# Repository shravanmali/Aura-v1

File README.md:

# Aura v1: Autonomous Companion Rover & Bedroom Satellite Pod

> *A comprehensive overview of the Aura v1 system architecture, bench-tested hardware, and software implementation in a single document.*

Hi! I'm Shravan Mali, an 18-year-old student and maker from India. This is **Aura v1**, an autonomous companion robot and bedroom satellite pod I am building from scratch for [Hack Club Fallen](https://fallen.hackclub.com/projects/prj_kV1Fde).

The idea behind Aura is to build a helpful robot for my room. It has two main parts:
1. **The Rover:** A 4WD mobile robot that tracks and follows me around the room using a camera, checks temperature and humidity, acts as a night motion sentry, and can count workout reps or play music on command.
2. **The Bedroom Satellite Pod:** A small stationary device plugged into the wall in my room. It connects to the rover over local Wi-Fi, listens for voice commands, controls my room's AC with an infrared transmitter, and lets me summon the rover to my room just by saying *"Aura, come here"*.

---

## Videos that shows physically working project.

I test and verify everything on my physical desk before moving to the next step. Here are three videos of the project working right on my desk:

1. **Live Vision Tracking & HUD:** [Watch on YouTube Shorts](https://youtube.com/shorts/xNkBhOSDpR0)  
   *(The rover tracks me by turning its BO motors left and right while streaming real-time temperature, humidity, and PIR motion data to my laptop screen).*
2. **DHT11 & PIR Motion Sensor Test:** [Watch on YouTube Shorts](https://youtube.com/shorts/FN-GSGQxdE8)  
   *(Bench testing room climate readings and motion detection on the ESP32-S3 before connecting the motor driver).*
3. **Face Centroid Tracking Loop:** [Watch on YouTube](https://youtu.be/JqQfvNIkbz4)  
   *(Testing real-time pixel offset calculations to steer the motors smoothly over serial).*

---

## What I've Built & Verified on My Desk

- **4WD Skid-Steer Motors:** 4x 200 RPM BO geared motors running on an L298N motor driver with ESP32 PWM soft-start so the motors don't jerk.
- **Real-Time Vision Following:** An OpenCV Python script (`vision_tracker.py`) that tracks human movement from a phone/webcam stream and steers the motors over USB serial at 115,200 baud.
- **Room Telemetry & Sentry:** A DHT11 sensor logging temperature and humidity every 2 seconds, plus a PIR motion sensor that triggers an alert badge if someone walks into the room.
- **Bedroom Satellite Pod PCB (v1.0):** A custom 2-layer PCB designed in KiCad. It houses the ESP32-C3 SuperMini, INMP441 mic, MAX98357A 3W amplifier, a 470µF bulk capacitor (to stop the speaker from rebooting the ESP32), an IR blaster, and an RGB LED ring. It passed KiCad DRC with **0 errors and 0 unconnected items**, and the fabrication Gerbers are ready.
- **Rover Carrier Board v1.5 Schematic:** The rover's motherboard schematic, verified with **0 ERC errors**. It separates high-current servo power from sensitive logic, adds I2S audio headers, and includes a 100kΩ/33kΩ resistor divider to monitor the 11.1V battery.
- **3D Chassis:** A dual-deck chassis designed in OpenSCAD to hold the motors, battery pack, electronics, and camera pan-tilt bracket.

---

## Features Coming Next (In Progress)

- **Exercise Rep Counter:** Using MediaPipe pose tracking on the camera to count push-ups or squats and check workout form.
- **Voice Music Playback:** Playing songs and voice responses through the I2S amplifier and 3W speaker via voice commands.
- **Auto-Docking:** Using the camera to detect an ArUco marker on a charging dock so the rover can drive itself to charge when the battery drops below 15% (`ADC <= 2940`).
- **Smart AC Control:** Blasting 940nm IR remote codes to turn the room AC on or off based on live temperature readings from the DHT11 sensor.

---

## How the System Works

```text
┌─────────────────────────────────────────────────────────────┐
│             AURA V1 AUTONOMOUS MOBILE ROVER                 │
│                                                             │
│   [ Raspberry Pi 4 Model B (1GB RAM) ]                      │
│   • High-Level Brain, OpenCV Computer Vision, Voice AI      │
│   • MediaPipe Pose Tracking (Exercise Rep Counter)          │
│   • ArUco Marker Autonomous Docking Navigation              │
│                              ▲                              │
│                              │ High-Speed UART / Serial     │
│                              ▼                              │
│   [ ESP32-S3 DevKit-C (N16R8) ]                             │
│   • Instant Real-Time Motor Kinematics (4WD PWM)            │
│   • 2-Axis Pan-Tilt Gimbal Servos (MG90S)                   │
│   • HC-SR04 Ultrasonic Emergency Braking (<1ms stop)        │
│   • 11.1V Battery Fuel Gauge ADC Monitor (Auto-dock <= 15%) │
└──────────────────────────────┬──────────────────────────────┘
                               ▲
                               │ Local Wi-Fi Mesh
                               ▼
┌─────────────────────────────────────────────────────────────┐
│             AURA BEDROOM SATELLITE POD                      │
│                                                             │
│   [ Stationary ESP32-C3 SuperMini Node (5V USB-C Powered) ] │
│   • 24/7 Room Listening Station (INMP441 + MAX98357A)       │
│   • Voice-Command Music & Media Playback (3W Speaker)       │
│   • Dedicated Room ID ("Aura, come here" summoning)         │
│   • 940nm IR Blaster + DHT11 Closed-Loop Room AC Control    │
│   • 470µF Bulk Capacitor (Prevents speaker inrush brownouts)│
└─────────────────────────────────────────────────────────────┘
```

---

## Custom KiCad Hardware & PCBs

All PCB design files, schematics, and manufacturing Gerbers are open-source in the [`hardware/`](hardware/) directory:

### 1. Bedroom Satellite Pod v1.0 (Fabrication-Ready PCB)
* **Directory:** [`hardware/Aura_Satellite_Pod/`](hardware/Aura_Satellite_Pod/)
* **Features:** 2-layer board, dual copper ground planes, 15.24mm DIP socket spacing for ESP32-C3 SuperMini, anti-brownout audio filtering, and 4 corner M3 mounting holes.
* **Status:** **0 DRC Errors, 0 Unconnected Nets**.
* **Files:** [Schematic PDF](hardware/Aura_Satellite_Pod/Aura_Satellite_Pod_Schematic.pdf) | [Manufacturing Gerbers Zip](hardware/Aura_Satellite_Pod/Gerbers_Aura_Satellite_Pod_v1.0.zip) | [3D Front Render](hardware/Aura_Satellite_Pod/3d_pcb_front.png) | [3D Back Render](hardware/Aura_Satellite_Pod/3d_pcb_back.png)

### 2. Rover Carrier Motherboard (Final Production PCB)
* **Directory:** [`hardware/Aura_Rover_Carrier_Final/`](hardware/Aura_Rover_Carrier_Final/)
* **Features:**
  * **Dual Isolated Power Rails:** Dedicated 5.1V logic rail (Buck #1 XL4015) for Raspberry Pi 4B & audio, and 5.0V actuator rail (Buck #2 LM2596S) with a 470µF bulk capacitor for MG90S servos and NeoPixels.
  * **Reverse Polarity & Auto-Docking Protection:** `AO3401A` / `IRF9540N` P-channel MOSFET circuit (0.03V drop) and `SS54` Schottky diode protecting dock charging contacts.
  * **High-Current Motor Rail:** Heavy screw terminal (`J_MOTOR`) powering L298N drive motors directly from 11.1V battery.
  * **Raspberry Pi Hardware Watchdog:** NPN transistor circuit (`Q4` 2N2222) to hardware-reset Linux via `GLOBAL_EN` if a lockup occurs.
  * **Visual Diagnostics & Alerts:** 3 power LEDs (Green 11.1V, Blue 5V, Amber 5V Servo), 5V active piezo buzzer, and I2C sensor expansion port.
* **Status:** **0 ERC Errors, 100% Routed (0 Unconnected Items), 0 DRC Violations, JLCPCB Manufacturing Gerbers Ready**.
* **Files:** [KiCad Schematic](hardware/Aura_Rover_Carrier_Final/Aura_Rover_Carrier_Final.kicad_sch) | [Schematic PDF](hardware/Aura_Rover_Carrier_Final/Aura_Rover_Carrier_Final_Schematic.pdf) | [PCB File](hardware/Aura_Rover_Carrier_Final/Aura_Rover_Carrier_Final.kicad_pcb) | [Manufacturing Gerbers Zip](hardware/Aura_Rover_Carrier_Final/Gerbers_Aura_Rover_Carrier_Final.zip) | [BOM CSV](hardware/Aura_Rover_Carrier_Final/Aura_Rover_Carrier_Final_BOM.csv) | [3D Top View](hardware/Aura_Rover_Carrier_Final/3d_pcb_carrier_top.png) | [3D Isometric View](hardware/Aura_Rover_Carrier_Final/3d_pcb_carrier_iso.png)

### 3. Historical Iteration Archive
All prior hardware revisions from prototype v1.0 through v1.5 are preserved in [`hardware/archive/`](hardware/archive/).

---

## Bill of Materials 

I keep two separate BOM files to be 100% transparent about what I already have on my desk and what I need funding for from Hack Club:

1. **[BOM.md](BOM.md) (Hack Club Fallen Grant Request):**  
   The exact 17 audited items requested through the Hack Club Fallen virtual card totaling **₹9,528 (~$100.67 USD)**, with clickable vendor purchase links for reviewers.
2. **[Aura_Master_BOM.csv](Aura_Master_BOM.csv) (Complete 0-to-100 Hardware Inventory):**  
   The complete system build (32 subsystems totaling ₹11,848), clearly separating:
   * **Owned by me (I have on my desk):** ₹2,320 (15 subsystems: ESP32-S3, BO motors, wheels, L298N, chassis, sensors, passives).
   * **Requested from Hack Club Fallen:** ₹9,528 (17 subsystems: Pi 4, CSI camera, MG90S servos, Li-ion 18650 pack, BMS, charger, satellite components).

---

## 3D Chassis Design

The chassis is designed in OpenSCAD with dual-deck standoffs to hold the battery pack, motor drivers, and boards securely:

---

## How to Run Locally

### 1. Upload Microcontroller Firmware
Open this repository in VS Code with PlatformIO:
```powershell
pio run --target upload --upload-port COM6
```
*(Or open `src/main.cpp` in Arduino IDE, select ESP32-S3 Dev Module, and upload).*

### 2. Start the Computer Vision Dashboard
1. Open DroidCam on your phone (or plug in a USB webcam).
2. Run the tracking script on your computer:
```powershell
python vision_tracker.py
```
* **Keyboard Driving:** Press **W / A / S / D** to drive manually, **Spacebar** to brake, **Q** to quit.
* **Auto-Follow:** Stand in front of the camera; the BO motors will automatically steer left/right to keep you centered.

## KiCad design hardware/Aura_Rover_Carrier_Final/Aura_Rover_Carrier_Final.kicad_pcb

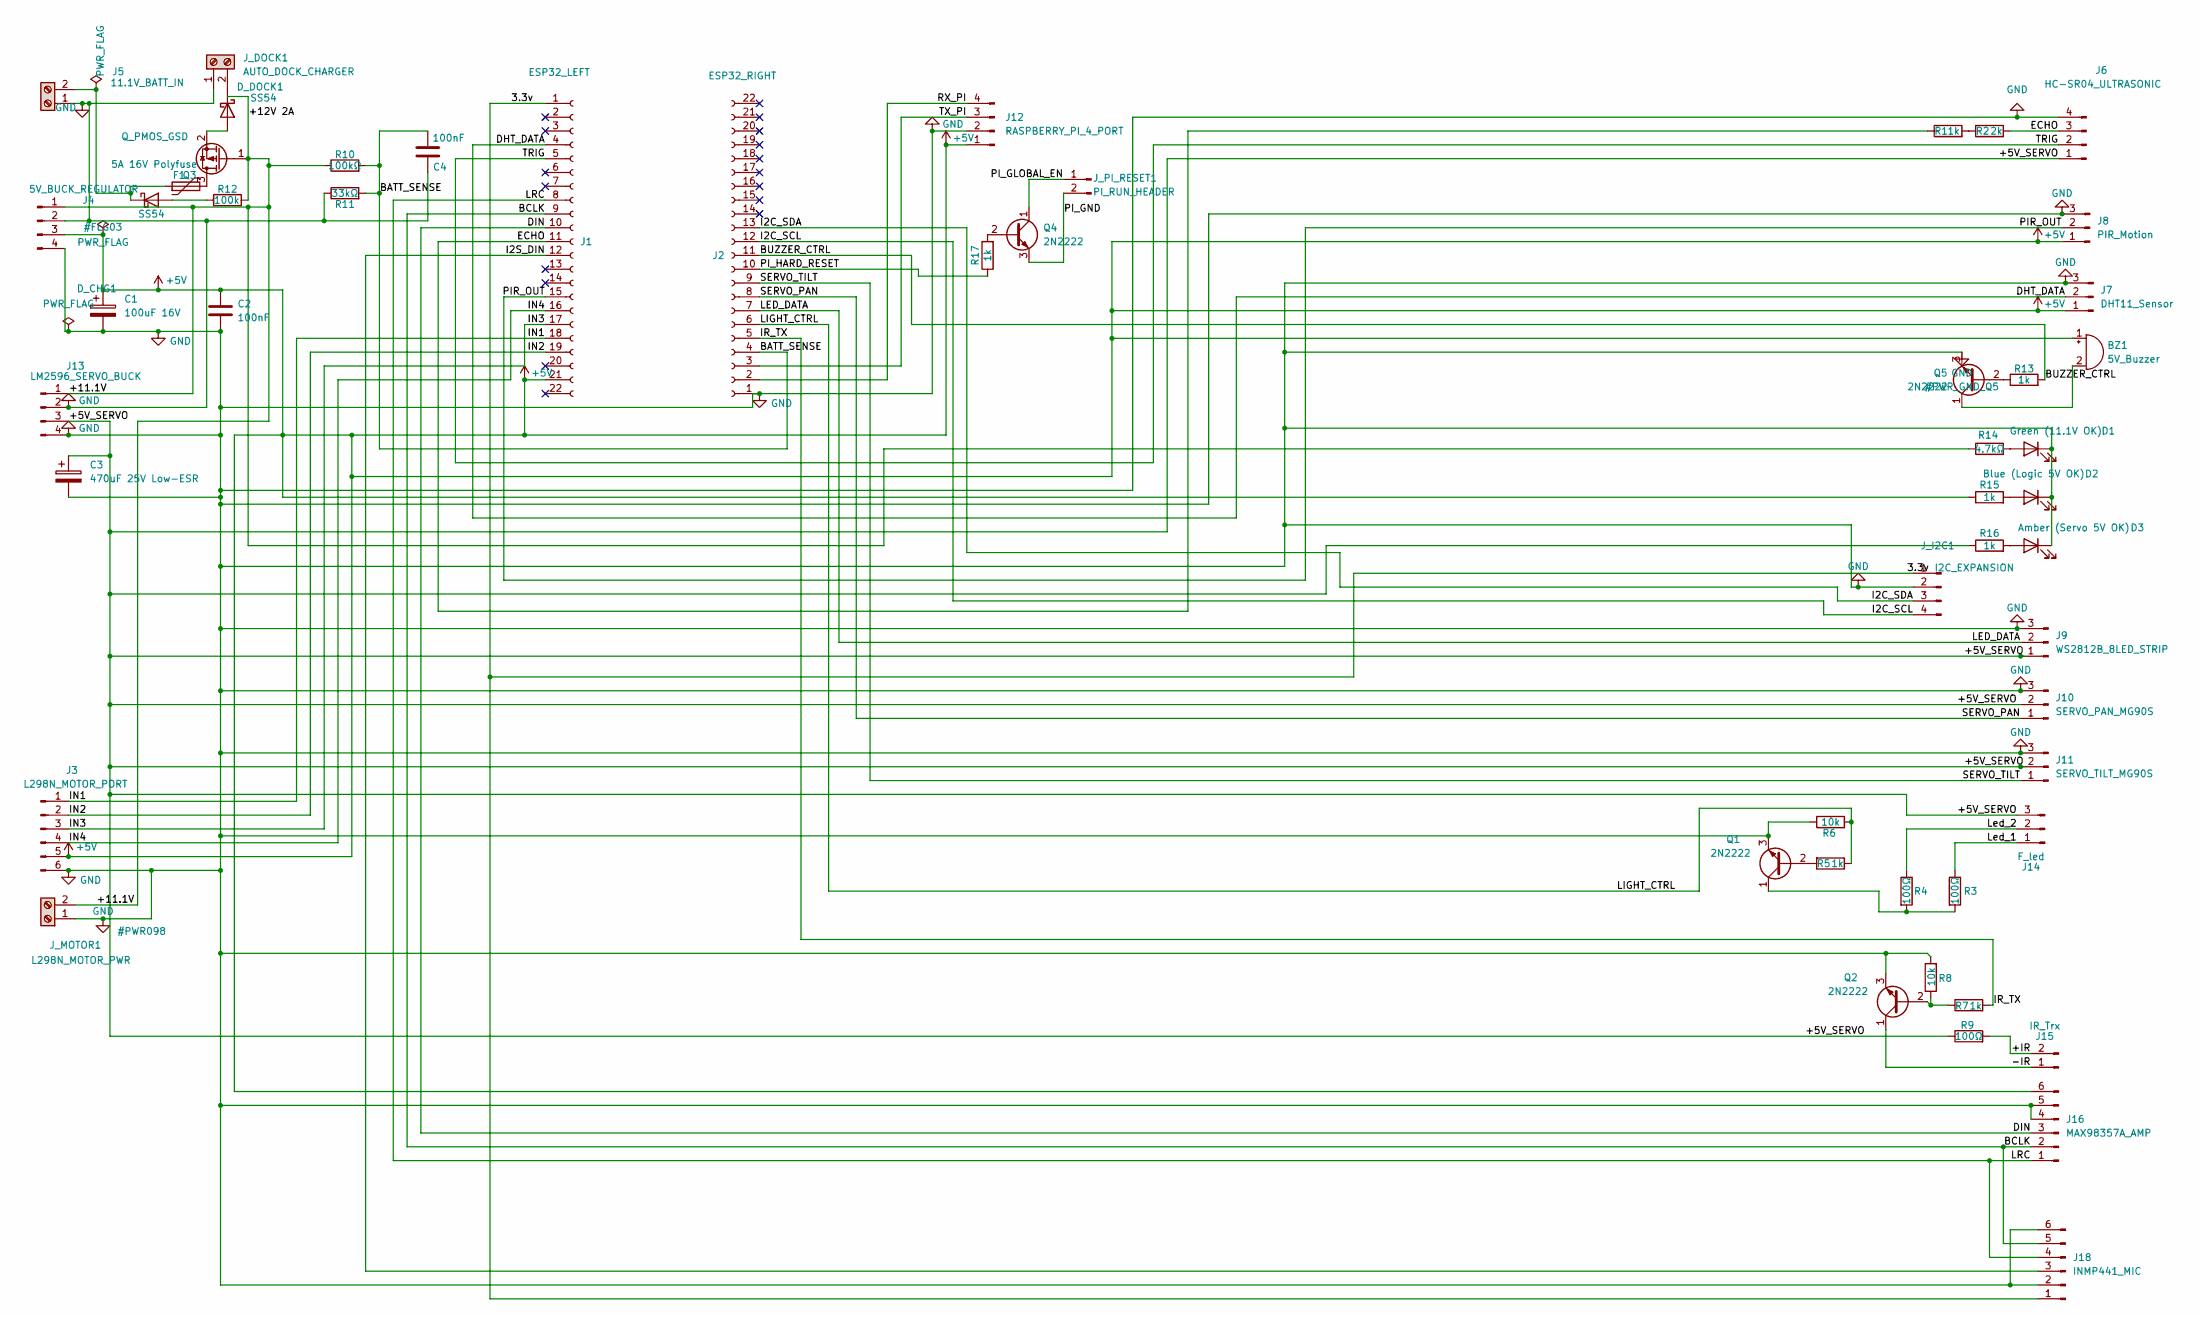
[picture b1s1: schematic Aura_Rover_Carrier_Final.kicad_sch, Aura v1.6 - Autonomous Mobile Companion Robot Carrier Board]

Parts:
BZ1: 5V_Buzzer; Buzzer_12x9.5RM7.6
C1: 100uF 16V; CP_Radial_D6.3mm_P2.50mm
C2, C4: 100nF; C_Disc_D5.0mm_W2.5mm_P5.00mm
C3: 470uF 25V Low-ESR; CP_Radial_D8.0mm_P3.50mm
D1: Green (11.1V OK); LED_D3.0mm
D2: Blue (Logic 5V OK); LED_D3.0mm
D3: Amber (Servo 5V OK); LED_D3.0mm
D_CHG1: SS54; D_DO-201AD_P15.24mm_Horizontal
D_DOCK1: SS54; D_DO-201AD_P15.24mm_Horizontal
F1: 5A 16V Polyfuse; Fuse_Bourns_MF-RG500
J1: ESP32_LEFT; PinSocket_1x22_P2.54mm_Vertical
J2: ESP32_RIGHT; PinSocket_1x22_P2.54mm_Vertical
J3: L298N_MOTOR_PORT; JST_XH_B6B-XH-A_1x06_P2.50mm_Vertical
J4: 5V_BUCK_REGULATOR; JST_XH_B4B-XH-A_1x04_P2.50mm_Vertical
J5: 11.1V_BATT_IN; TerminalBlock_Phoenix_MKDS-1,5-2-5.08_1x02_P5.08mm_Horizont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
J6: HC-SR04_ULTRASONIC; JST_XH_B4B-XH-A_1x04_P2.50mm_Vertical
J7: DHT11_Sensor; JST_XH_B3B-XH-A_1x03_P2.50mm_Vertical
J8: PIR_Motion; JST_XH_B3B-XH-A_1x03_P2.50mm_Vertical
J9: WS2812B_8LED_STRIP; JST_XH_B3B-XH-A_1x03_P2.50mm_Vertical
J10: SERVO_PAN_MG90S; PinHeader_1x03_P2.54mm_Vertical
J11: SERVO_TILT_MG90S; PinHeader_1x03_P2.54mm_Vertical
J12: RASPBERRY_PI_4_PORT; JST_XH_B4B-XH-A_1x04_P2.50mm_Vertical
J13: LM2596_SERVO_BUCK; JST_XH_B4B-XH-A_1x04_P2.50mm_Vertical
J14: F_led; JST_XH_B3B-XH-A_1x03_P2.50mm_Vertical
J15: IR_Trx; JST_XH_B2B-XH-A_1x02_P2.50mm_Vertical
J16: MAX98357A_AMP; PinSocket_1x06_P2.54mm_Vertical
J18: INMP441_MIC; PinSocket_1x06_P2.54mm_Vertical
J_DOCK1: AUTO_DOCK_CHARGER; TerminalBlock_Phoenix_MKDS-1,5-2-5.08_1x02_P5.08mm_Horizont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
J_I2C1: I2C_EXPANSION; JST_XH_B4B-XH-A_1x04_P2.50mm_Vertical
J_MOTOR1: L298N_MOTOR_PWR; TerminalBlock_Phoenix_MKDS-1,5-2-5.08_1x02_P5.08mm_Horizont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
J_PI_RESET1: PI_RUN_HEADER; PinHeader_1x02_P2.54mm_Vertical
Q1, Q2, Q4, Q5: 2N2222; TO-92_Inline
Q3: Q_PMOS_GSD; TO-220-3_Vertical
R1, R5, R7, R13, R15, R16, R17: 1k; R_Axial_DIN0207_L6.3mm_D2.5mm_P7.62mm_Horizontal
R2: 2k; R_Axial_DIN0207_L6.3mm_D2.5mm_P7.62mm_Horizontal
R3, R4, R9: 100Ω; R_Axial_DIN0207_L6.3mm_D2.5mm_P7.62mm_Horizontal
R6, R8: 10k; R_Axial_DIN0207_L6.3mm_D2.5mm_P7.62mm_Horizontal
R10: 100kΩ; R_Axial_DIN0207_L6.3mm_D2.5mm_P7.62mm_Horizontal
R11: 33kΩ; R_Axial_DIN0207_L6.3mm_D2.5mm_P7.62mm_Horizontal
R12: 100k; R_Axial_DIN0207_L6.3mm_D2.5mm_P7.62mm_Horizontal
R14: 4.7kΩ; R_Axial_DIN0207_L6.3mm_D2.5mm_P7.62mm_Horizontal

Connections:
+5V: BZ1.1 (+), C1.1, C2.1, J1.21, J3.5, J4.3, J7.1, J8.1, J12.1, J16.6, R15.1
/3.3v: J1.1, J18.1, J_I2C1.1
/+5V_SERVO: C3.1, J6.1, J9.1, J10.2, J11.2, J13.3, J14.3, R9.1, R16.1
/+11.1V: J4.1, J13.1, J_MOTOR1.2, Q3.1 (G), R10.1, R12.2, R14.1
/+IR: J15.2, R9.2
/-IR: J15.1, Q2.1 (C)
/BATT_SENSE: C4.2, J2.4, R10.2, R11.2
/BCLK: J1.9, J16.2, J18.5
/BUZZER_CTRL: J2.11, R13.2
/DHT_DATA: J1.4, J7.2
/DIN: J1.10, J16.3
/ECHO: J1.11, J6.3, R1.1, R2.2
/I2C_SCL: J2.12, J_I2C1.4
/I2C_SDA: J2.13, J_I2C1.3
/I2S_DIN: J1.12, J18.3
/IN1: J1.18, J3.1
/IN2: J1.19, J3.2
/IN3: J1.17, J3.3
/IN4: J1.16, J3.4
/IR_TX: J2.5, R7.2
/LED_DATA: J2.7, J9.2
/LIGHT_CTRL: J2.6, R5.1, R6.2
/LRC: J1.8, J16.1, J18.4
/Led_1: J14.1, R3.1
/Led_2: J14.2, R4.1
/PIR_OUT: J1.15, J8.2
/PI_GLOBAL_EN: J_PI_RESET1.1, Q4.1 (C)
/PI_GND: J_PI_RESET1.2, Q4.3 (E)
/PI_HARD_RESET: J2.10, R17.1
/RX_PI: J2.2, J12.4
/SERVO_PAN: J2.8, J10.1
/SERVO_TILT: J2.9, J11.1
/TRIG: J1.5, J6.2
/TX_PI: J2.3, J12.3
GND: C1.2, C2.2, C3.2, C4.1, D1.1 (K), D2.1 (K), D3.1 (K), J2.1, J3.6, J4.2, J4.4, J5.1, J6.4, J7.3, J8.3, J9.3, J10.3, J11.3, J12.2, J13.2, J13.4, J16.4, J16.5, J18.2, J18.6, J_DOCK1.1, J_I2C1.2, J_MOTOR1.1, Q1.3 (E), Q2.3 (E), Q5.3 (E), R6.1, R8.2, R11.1; also elsewhere on the board
unnamed: BZ1.2 (-), Q5.1 (C)
unnamed: D1.2 (A), R14.2
unnamed: D2.2 (A), R15.2
unnamed: D3.2 (A), R16.2
unnamed: D_CHG1.2 (A), R12.1
unnamed: D_CHG1.1 (K), F1.1, J5.2
unnamed: D_DOCK1.2 (A), Q3.2 (S)
unnamed: D_DOCK1.1 (K), J_DOCK1.2
unnamed: Q1.2 (B), R5.2
unnamed: Q1.1 (C), R3.2, R4.2
unnamed: Q2.2 (B), R7.1, R8.1
unnamed: F1.2, Q3.3 (D)
unnamed: Q4.2 (B), R17.2
unnamed: Q5.2 (B), R13.1
unnamed: R1.2, R2.1

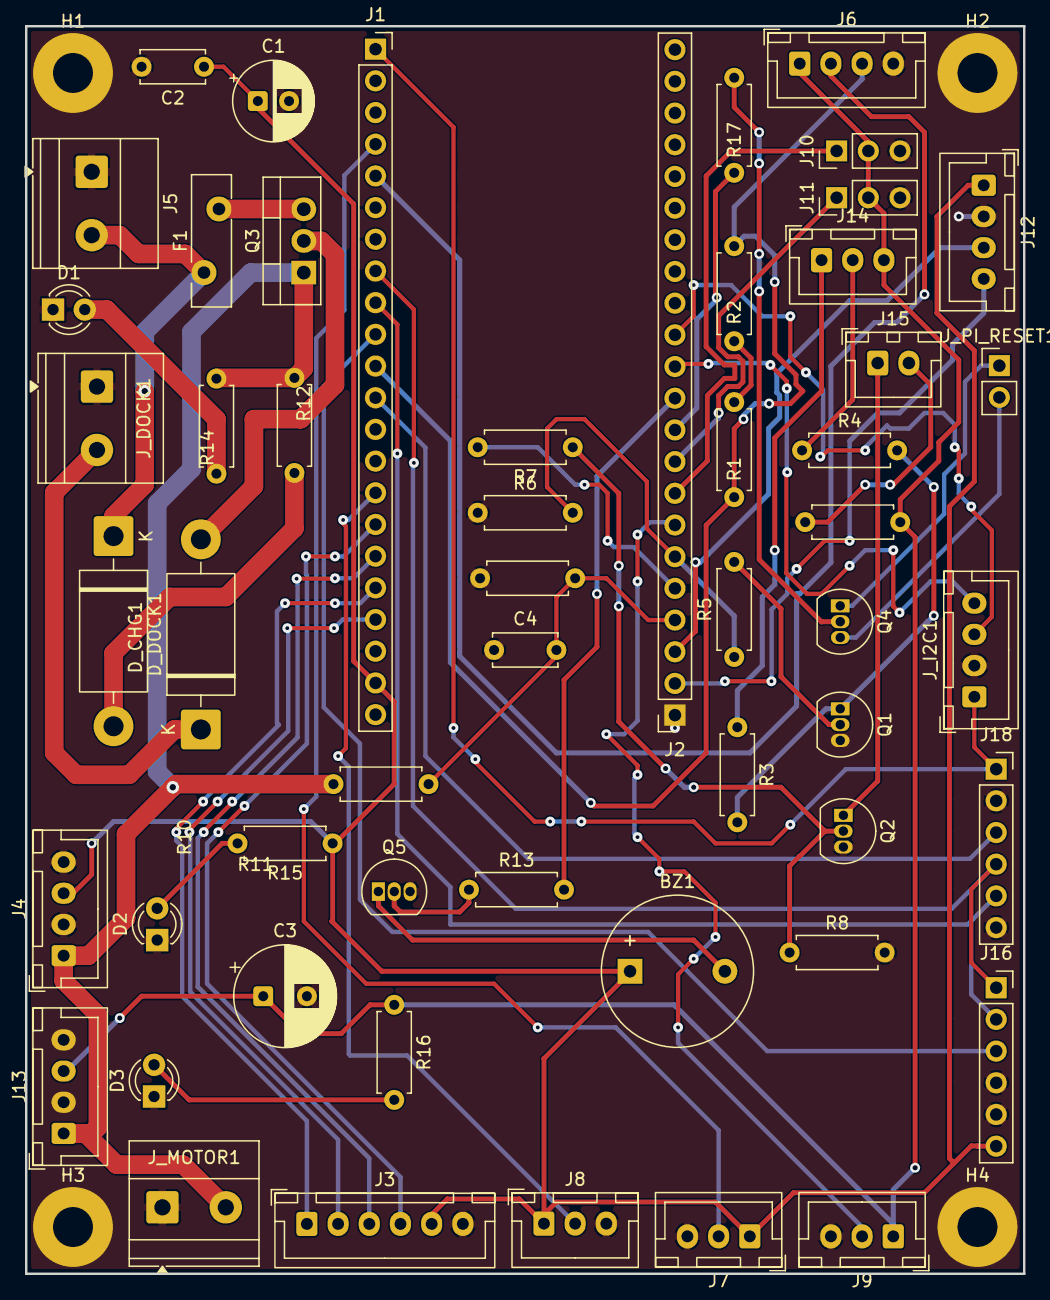
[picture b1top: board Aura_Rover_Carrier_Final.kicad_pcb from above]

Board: 2 copper layers, 80.0 x 100.0 mm, 58 parts (0 on the bottom side), 50 nets.

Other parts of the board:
H1, H2, H3, H4: M3_Mounting_Hole; MountingHole_3.2mm_M3_Pad

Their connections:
GND: H1.1, H2.1, H3.1, H4.1; also elsewhere on the board

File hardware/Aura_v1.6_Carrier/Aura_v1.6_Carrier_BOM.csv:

Item,Reference,Value,Footprint
1,BZ1,5V_ACTIVE_BUZZER,Buzzer_Beeper:Buzzer_12x9.5RM7.6
2,C1,100uF 16V,Capacitor_THT:CP_Radial_D6.3mm_P2.50mm
3,C2,100nF,Capacitor_THT:C_Disc_D5.0mm_W2.5mm_P5.00mm
4,C3,470uF 25V Low-ESR,Capacitor_THT:CP_Radial_D8.0mm_P3.50mm
5,C4,100nF,Capacitor_THT:C_Disc_D5.0mm_W2.5mm_P5.00mm
6,D1,Green (11.1V OK),LED_THT:LED_D3.0mm
7,D2,Blue (Logic 5V OK),LED_THT:LED_D3.0mm
8,D3,Amber (Servo 5V OK),LED_THT:LED_D3.0mm
9,D_DOCK1,SS54,Diode_THT:D_DO-201AD_P15.24mm_Horizontal
9b,D_CHG1,SS54,Diode_THT:D_DO-201AD_P15.24mm_Horizontal
10,F1,5A 16V Polyfuse,Fuse:Fuse_Bourns_MF-RHT500
11,H1,M3_Mounting_Hole,MountingHole:MountingHole_3.2mm_M3_Pad
12,H2,M3_Mounting_Hole,MountingHole:MountingHole_3.2mm_M3_Pad
13,H3,M3_Mounting_Hole,MountingHole:MountingHole_3.2mm_M3_Pad
14,H4,M3_Mounting_Hole,MountingHole:MountingHole_3.2mm_M3_Pad
15,J1,ESP32_LEFT,Connector_PinSocket_2.54mm:PinSocket_1x22_P2.54mm_Vertical
16,J2,ESP32_RIGHT,Connector_PinSocket_2.54mm:PinSocket_1x22_P2.54mm_Vertical
17,J3,L298N_MOTOR_PORT,Connector_JST:JST_XH_B6B-XH-A_1x06_P2.50mm_Vertical
18,J4,5V_BUCK_REGULATOR,Connector_JST:JST_XH_B4B-XH-A_1x04_P2.50mm_Vertical
19,J5,11.1V_BATT_IN,"TerminalBlock_Phoenix:TerminalBlock_Phoenix_MKDS-1,5-2-5.08_1x02_P5.08mm_Horizontal"
20,J6,HC-SR04_ULTRASONIC,Connector_JST:JST_XH_B4B-XH-A_1x04_P2.50mm_Vertical
21,J7,DHT11_Sensor,Connector_JST:JST_XH_B3B-XH-A_1x03_P2.50mm_Vertical
22,J8,PIR_Motion,Connector_JST:JST_XH_B3B-XH-A_1x03_P2.50mm_Vertical
23,J9,WS2812B_8LED_STRIP,Connector_JST:JST_XH_B3B-XH-A_1x03_P2.50mm_Vertical
24,J10,SERVO_PAN_MG90S,Connector_PinHeader_2.54mm:PinHeader_1x03_P2.54mm_Vertical
25,J11,SERVO_TILT_MG90S,Connector_PinHeader_2.54mm:PinHeader_1x03_P2.54mm_Vertical
26,J12,RASPBERRY_PI_4_PORT,Connector_JST:JST_XH_B4B-XH-A_1x04_P2.50mm_Vertical
27,J13,LM2596_SERVO_BUCK,Connector_JST:JST_XH_B4B-XH-A_1x04_P2.50mm_Vertical
28,J14,F_led,Connector_JST:JST_XH_B3B-XH-A_1x03_P2.50mm_Vertical
29,J15,IR_Trx,Connector_JST:JST_XH_B2B-XH-A_1x02_P2.50mm_Vertical
30,J16,MAX98357A_AMP,Connector_PinSocket_2.54mm:PinSocket_1x06_P2.54mm_Vertical
31,J17,SPEAKER_4OHM,"TerminalBlock_Phoenix:TerminalBlock_Phoenix_MKDS-1,5-2-5.08_1x02_P5.08mm_Horizontal"
32,J18,INMP441_MIC,Connector_PinSocket_2.54mm:PinSocket_1x06_P2.54mm_Vertical
33,J_DOCK1,AUTO_DOCK_CHARGER,"TerminalBlock_Phoenix:TerminalBlock_Phoenix_MKDS-1,5-2-5.08_1x02_P5.08mm_Horizontal"
34,J_I2C1,I2C_EXPANSION,Connector_JST:JST_XH_B4B-XH-A_1x04_P2.50mm_Vertical
35,J_MOTOR1,L298N_MOTOR_PWR,"TerminalBlock_Phoenix:TerminalBlock_Phoenix_MKDS-1,5-2-5.08_1x02_P5.08mm_Horizontal"
36,J_PI_RESET1,PI_RUN_HEADER,Connector_PinHeader_2.54mm:PinHeader_1x02_P2.54mm_Vertical
37,Q1,2N2222,Package_TO_SOT_THT:TO-92_Inline
38,Q2,2N2222,Package_TO_SOT_THT:TO-92_Inline
39,Q3,Q_PMOS_GSD,Package_TO_SOT_THT:TO-220-3_Vertical
40,Q4,2N2222,Package_TO_SOT_THT:TO-92_Inline
41,Q5,2N2222,Package_TO_SOT_THT:TO-92_Inline
42,R1,1k,Resistor_THT:R_Axial_DIN0207_L6.3mm_D2.5mm_P10.16mm_Horizontal
43,R2,2k,Resistor_THT:R_Axial_DIN0207_L6.3mm_D2.5mm_P10.16mm_Horizontal
44,R3,100Ω,Resistor_THT:R_Axial_DIN0207_L6.3mm_D2.5mm_P10.16mm_Horizontal
45,R4,100Ω,Resistor_THT:R_Axial_DIN0207_L6.3mm_D2.5mm_P10.16mm_Horizontal
46,R5,1k,Resistor_THT:R_Axial_DIN0207_L6.3mm_D2.5mm_P10.16mm_Horizontal
47,R6,10k,Resistor_THT:R_Axial_DIN0207_L6.3mm_D2.5mm_P10.16mm_Horizontal
48,R7,1k,Resistor_THT:R_Axial_DIN0207_L6.3mm_D2.5mm_P10.16mm_Horizontal
49,R8,10k,Resistor_THT:R_Axial_DIN0207_L6.3mm_D2.5mm_P10.16mm_Horizontal
50,R9,100Ω,Resistor_THT:R_Axial_DIN0207_L6.3mm_D2.5mm_P10.16mm_Horizontal
51,R11,33kΩ,Resistor_THT:R_Axial_DIN0207_L6.3mm_D2.5mm_P10.16mm_Horizontal
52,R12,100k,Resistor_THT:R_Axial_DIN0207_L6.3mm_D2.5mm_P10.16mm_Horizontal
53,R13,4.7kΩ,Resistor_THT:R_Axial_DIN0207_L6.3mm_D2.5mm_P10.16mm_Horizontal
54,R14,1k,Resistor_THT:R_Axial_DIN0207_L6.3mm_D2.5mm_P10.16mm_Horizontal
55,R15,1k,Resistor_THT:R_Axial_DIN0207_L6.3mm_D2.5mm_P10.16mm_Horizontal
56,R17,1k,Resistor_THT:R_Axial_DIN0207_L6.3mm_D2.5mm_P10.16mm_Horizontal
57,R18,1k,Resistor_THT:R_Axial_DIN0207_L6.3mm_D2.5mm_P10.16mm_Horizontal

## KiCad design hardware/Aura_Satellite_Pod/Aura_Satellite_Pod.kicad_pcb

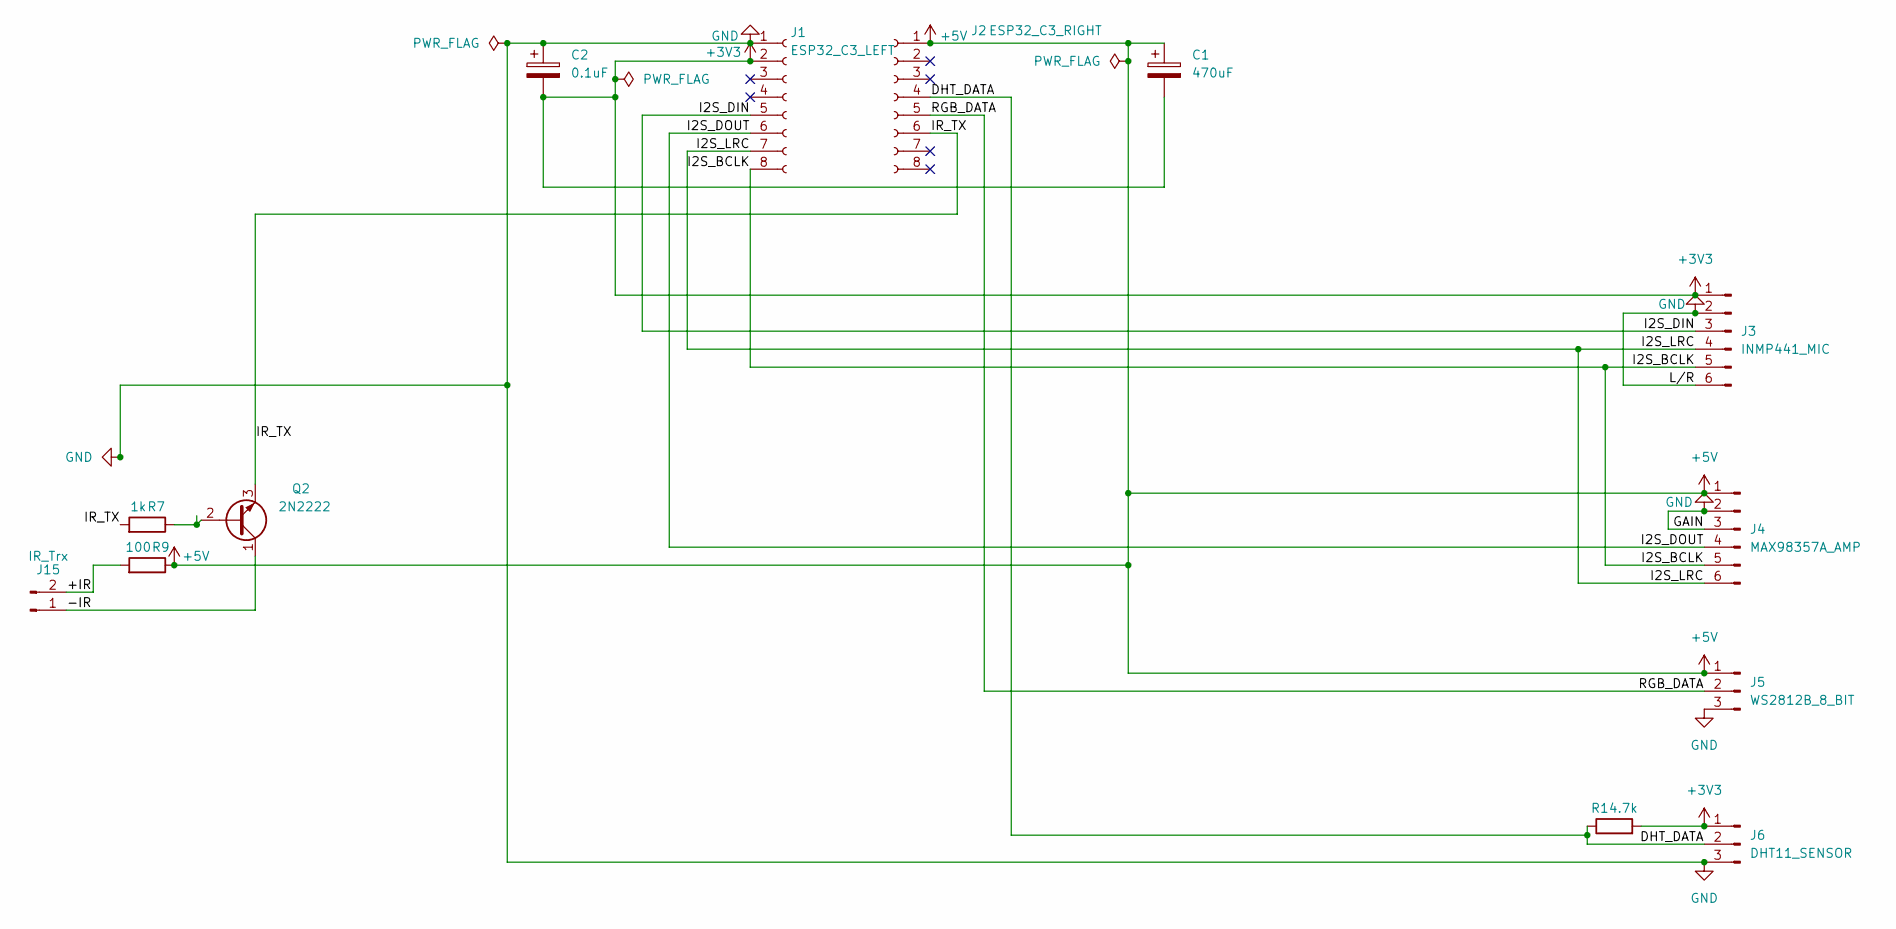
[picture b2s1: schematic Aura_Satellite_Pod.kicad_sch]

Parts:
C1: 470uF; CP_Radial_D8.0mm_P3.50mm
C2: 0.1uF; C_Disc_D4.3mm_W1.9mm_P5.00mm
J1: ESP32_C3_LEFT; PinSocket_1x08_P2.54mm_Vertical
J2: ESP32_C3_RIGHT; PinSocket_1x08_P2.54mm_Vertical
J3: INMP441_MIC; PinHeader_1x06_P2.54mm_Vertical
J4: MAX98357A_AMP; PinHeader_1x06_P2.54mm_Vertical
J5: WS2812B_8_BIT; PinHeader_1x03_P2.54mm_Vertical
J6: DHT11_SENSOR; PinHeader_1x03_P2.54mm_Vertical
J15: IR_Trx; PinHeader_1x02_P2.54mm_Vertical
Q2: 2N2222; TO-92_Inline
R1: 4.7k; R_Axial_DIN0207_L6.3mm_D2.5mm_P7.62mm_Horizontal
R7: 1k; R_Axial_DIN0207_L6.3mm_D2.5mm_P7.62mm_Horizontal
R9: 100; R_Axial_DIN0207_L6.3mm_D2.5mm_P7.62mm_Horizontal

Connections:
+3V3: C1.2, C2.2, J1.2, J3.1, J6.1, R1.2
+5V: C1.1, J2.1, J4.1, J5.1, R9.1
/+IR: J15.2, R9.2
/-IR: J15.1, Q2.1 (C)
/DHT_DATA: J2.4, J6.2, R1.1
/I2S_BCLK: J1.8, J3.5, J4.5
/I2S_DIN: J1.5, J3.3
/I2S_DOUT: J1.6, J4.4
/I2S_LRC: J1.7, J3.4, J4.6
/IR_TX: J2.6, Q2.3 (E), R7.2
/RGB_DATA: J2.5, J5.2
GND: C2.1, J1.1, J3.2, J3.6, J4.2, J4.3, J5.3, J6.3
unnamed: Q2.2 (B), R7.1

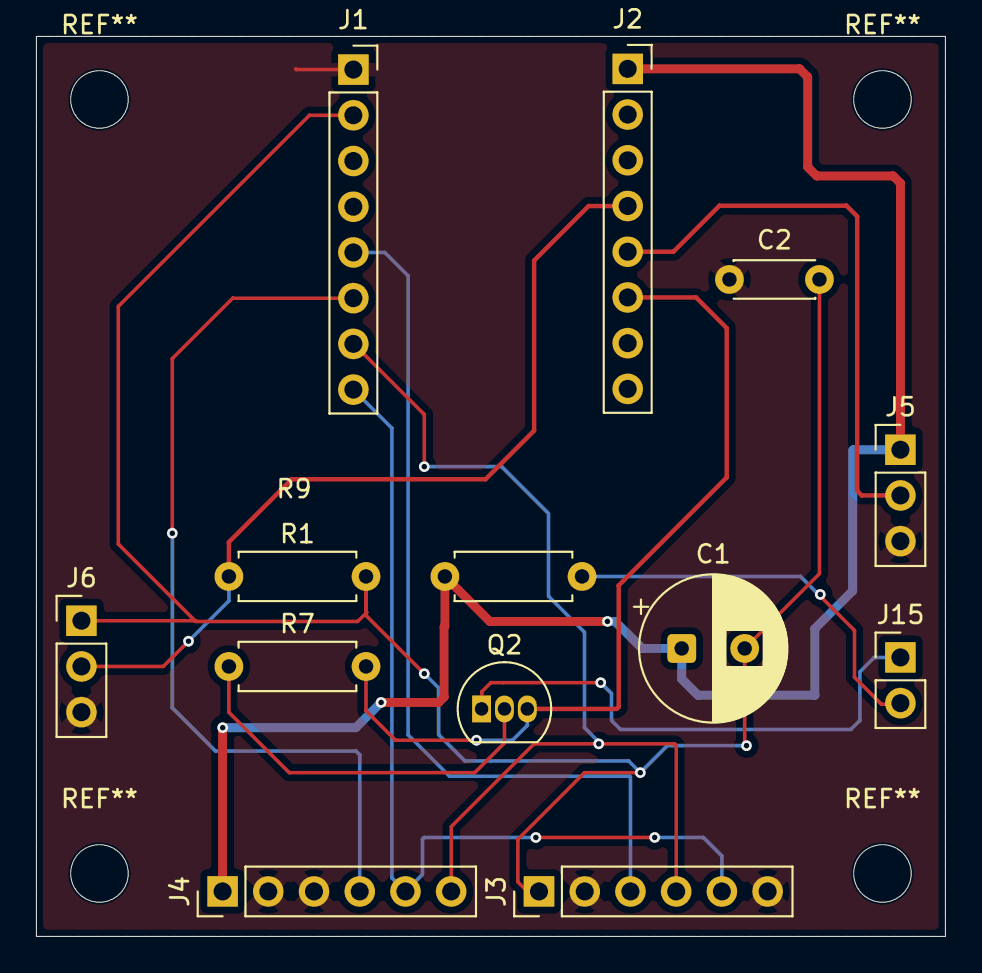
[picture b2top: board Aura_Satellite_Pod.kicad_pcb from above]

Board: 2 copper layers, 50.5 x 50.0 mm, 13 parts (0 on the bottom side), 13 nets.

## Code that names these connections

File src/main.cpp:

// =============================================================================
// Aura v1.6 - Autonomous Mobile Companion Robot Production Firmware
// Hardware: ESP32-S3 DevKit-C (N16R8) on Aura v1.6 Carrier PCB
// Author: Shravan Mali (Hack Club Fallen - Aura v1)
// =============================================================================

#include <Arduino.h>
#include <DHT.h>

// -----------------------------------------------------------------------------
// Pin Definitions (Directly mapped to Aura v1.6 Carrier PCB)
// -----------------------------------------------------------------------------
// L298N 4WD Motor Driver (J3 / J_MOTOR)
const int PIN_MOTOR_IN1    = 10; // J1 Pin 18 (Left Forward)
const int PIN_MOTOR_IN2    = 11; // J1 Pin 19 (Left Reverse)
const int PIN_MOTOR_IN3    = 12; // J1 Pin 20 (Right Forward)
const int PIN_MOTOR_IN4    = 13; // J1 Pin 21 (Right Reverse)

// Pan-Tilt Gimbal Servos (LEDC PWM on ESP32-S3)
const int PIN_SERVO_PAN    = 40; // J2 Pin 8
const int PIN_SERVO_TILT   = 39; // J2 Pin 9
const int SERVO_PAN_CH     = 0;
const int SERVO_TILT_CH    = 1;

// Actuator & Diagnostic Outputs
const int PIN_BUZZER       = 38; // J2 Pin 10 (via Q5 2N2222)
const int PIN_LIGHT_CTRL   = 42; // J2 Pin 6  (via Q1 2N2222)
const int PIN_PI_RESET     = 37; // J2 Pin 11 (via Q4 2N2222 to Pi GLOBAL_EN)

// Sensors
const int PIN_DHT          = 4;  // J1 Pin 4  (DHT11)
const int PIN_PIR          = 14; // J1 Pin 22 (HC-SR501)
const int PIN_BATT_SENSE   = 1;  // J2 Pin 4  (ADC1_CH0 via 100k/33k divider)

#define DHTTYPE DHT11
DHT dht(PIN_DHT, DHTTYPE);

// State Variables
float battery_voltage = 0.0;
float temperature = 0.0;
float humidity = 0.0;
bool pir_detected = false;

// Timers
unsigned long last_command_time = 0;
unsigned long last_telemetry_time = 0;
unsigned long last_pi_heartbeat = 0;
const unsigned long WATCHDOG_TIMEOUT_MS = 600;       // Auto-stop motors if Pi disconnects
const unsigned long PI_HARD_RESET_TIMEOUT_MS = 30000; // 30 sec freeze triggers reboot

// -----------------------------------------------------------------------------
// Servo Control using ESP32-S3 Hardware PWM (50Hz, 16-bit resolution)
// -----------------------------------------------------------------------------
void write_servo_angle(int channel, int angle_deg) {
  angle_deg = constrain(angle_deg, 0, 180);
  // 50Hz period = 20ms. 0 deg = 0.5ms (1638 counts), 180 deg = 2.5ms (8192 counts)
  uint32_t duty = 1638 + (angle_deg * (8192 - 1638) / 180);
  ledcWrite(channel, duty);
}

// -----------------------------------------------------------------------------
// Audible Buzzer Chirp Helper
// -----------------------------------------------------------------------------
void beep(int duration_ms, int freq_hz = 2000) {
  tone(PIN_BUZZER, freq_hz, duration_ms);
  delay(duration_ms);
  noTone(PIN_BUZZER);
}

// -----------------------------------------------------------------------------
// Read Battery Voltage via 100kΩ / 33kΩ Resistor Divider (R10 / R11)
// Ratio = (100k + 33k) / 33k = 4.0303
// -----------------------------------------------------------------------------
float read_battery_voltage() {
  uint32_t raw_adc = analogRead(PIN_BATT_SENSE);
  float pin_voltage = (raw_adc / 4095.0) * 3.30;
  return pin_voltage * 4.0303;
}

// -----------------------------------------------------------------------------
// 4WD Motor Skid-Steer Controller
// -----------------------------------------------------------------------------
void drive_motors(int left_cmd, int right_cmd) {
  // Left Motors (IN1 / IN2)
  if (left_cmd > 0) {
    digitalWrite(PIN_MOTOR_IN1, HIGH);
    digitalWrite(PIN_MOTOR_IN2, LOW);
  } else if (left_cmd < 0) {
    digitalWrite(PIN_MOTOR_IN1, LOW);
    digitalWrite(PIN_MOTOR_IN2, HIGH);
  } else {
    digitalWrite(PIN_MOTOR_IN1, LOW);
    digitalWrite(PIN_MOTOR_IN2, LOW);
  }

  // Right Motors (IN3 / IN4)
  if (right_cmd > 0) {
    digitalWrite(PIN_MOTOR_IN3, HIGH);
    digitalWrite(PIN_MOTOR_IN4, LOW);
  } else if (right_cmd < 0) {
    digitalWrite(PIN_MOTOR_IN3, LOW);
    digitalWrite(PIN_MOTOR_IN4, HIGH);
  } else {
    digitalWrite(PIN_MOTOR_IN3, LOW);
    digitalWrite(PIN_MOTOR_IN4, LOW);
  }
}

// -----------------------------------------------------------------------------
// Hardware Raspberry Pi Emergency Reboot
// -----------------------------------------------------------------------------
void trigger_pi_hardware_reboot() {
  Serial.println("[SAFETY] Raspberry Pi frozen! Pulling GLOBAL_EN low...");
  beep(300, 1000);
  
  // Pull Pi GLOBAL_EN to GND for 250ms via Q4
  digitalWrite(PIN_PI_RESET, HIGH);
  delay(250);
  digitalWrite(PIN_PI_RESET, LOW);

  last_pi_heartbeat = millis(); // Reset timer to allow Pi 30 seconds to boot
  beep(100, 2200);
}

// -----------------------------------------------------------------------------
// Arduino Setup
// -----------------------------------------------------------------------------
void setup() {
  Serial.begin(115200);
  delay(200);

  // Configure Motor Outputs
  pinMode(PIN_MOTOR_IN1, OUTPUT);
  pinMode(PIN_MOTOR_IN2, OUTPUT);
  pinMode(PIN_MOTOR_IN3, OUTPUT);
  pinMode(PIN_MOTOR_IN4, OUTPUT);
  drive_motors(0, 0);

  // Configure Actuator Pins
  pinMode(PIN_BUZZER, OUTPUT);
  pinMode(PIN_LIGHT_CTRL, OUTPUT);
  pinMode(PIN_PI_RESET, OUTPUT);
  digitalWrite(PIN_LIGHT_CTRL, LOW);
  digitalWrite(PIN_PI_RESET, LOW);

  // Sensors & ADC
  pinMode(PIN_PIR, INPUT);
  analogReadResolution(12);
  dht.begin();

  // Configure Hardware PWM for Pan-Tilt Servos (50Hz, 16-bit)
  ledcSetup(SERVO_PAN_CH, 50, 16);
  ledcAttachPin(PIN_SERVO_PAN, SERVO_PAN_CH);
  ledcSetup(SERVO_TILT_CH, 50, 16);
  ledcAttachPin(PIN_SERVO_TILT, SERVO_TILT_CH);

  write_servo_angle(SERVO_PAN_CH, 90);  // Center forward
  write_servo_angle(SERVO_TILT_CH, 90); // Center level

  // Aura Power-On Chime
  beep(80, 1800);
  delay(50);
  beep(150, 2400);

  last_command_time = millis();
  last_pi_heartbeat = millis();
  Serial.println("AURA_V1.6_ONLINE");
}

// -----------------------------------------------------------------------------
// Main Execution Loop
// -----------------------------------------------------------------------------
void loop() {
  // 1. Process Serial Commands from Raspberry Pi
  while (Serial.available() > 0) {
    String cmd = Serial.readStringUntil('\n');
    cmd.trim();
    last_command_time = millis();

    if (cmd == "HEARTBEAT") {
      last_pi_heartbeat = millis();
    } else if (cmd == "F" || cmd == "f") {
      drive_motors(1, 1);
    } else if (cmd == "B" || cmd == "b") {
      drive_motors(-1, -1);
    } else if (cmd == "L" || cmd == "l") {
      drive_motors(-1, 1);
    } else if (cmd == "R" || cmd == "r") {
      drive_motors(1, -1);
    } else if (cmd == "S" || cmd == "s" || cmd == "O" || cmd == "o") {
      drive_motors(0, 0);
    } else if (cmd.startsWith("DRIVE:")) {
      int comma_idx = cmd.indexOf(',');
      if (comma_idx > 6) {
        int l = cmd.substring(6, comma_idx).toInt();
        int r = cmd.substring(comma_idx + 1).toInt();
        drive_motors(l, r);
      }
    } else if (cmd.startsWith("GIMBAL:")) {
      int comma_idx = cmd.indexOf(',');
      if (comma_idx > 7) {
        int p = cmd.substring(7, comma_idx).toInt();
        int t = cmd.substring(comma_idx + 1).toInt();
        write_servo_angle(SERVO_PAN_CH, constrain(p, 15, 165));
        write_servo_angle(SERVO_TILT_CH, constrain(t, 40, 140));
      }
    } else if (cmd == "LIGHT_ON") {
      digitalWrite(PIN_LIGHT_CTRL, HIGH);
    } else if (cmd == "LIGHT_OFF") {
      digitalWrite(PIN_LIGHT_CTRL, LOW);
    } else if (cmd == "BEEP") {
      beep(100, 2200);
    }
  }

  // 2. Safety Timeout: Auto-stop motors if no drive packet received in 600ms
  if (millis() - last_command_time > WATCHDOG_TIMEOUT_MS) {
    drive_motors(0, 0);
  }

  // 3. Periodic Telemetry Stream (Every 1000ms)
  if (millis() - last_telemetry_time >= 1000) {
    last_telemetry_time = millis();
    battery_voltage = read_battery_voltage();
    pir_detected = (digitalRead(PIN_PIR) == HIGH);

    float t = dht.readTemperature();
    float h = dht.readHumidity();
    if (!isnan(t)) temperature = t;
    if (!isnan(h)) humidity = h;

    Serial.printf("[TELEM] BATT:%.2f|T:%.1f|H:%.1f|PIR:%d\n", 
                  battery_voltage, temperature, humidity, pir_detected ? 1 : 0);

    // Low battery warning (< 10.0V on 3S pack)
    if (battery_voltage < 10.0 && battery_voltage > 7.0) {
      beep(80, 800);
    }
  }

  // 4. Raspberry Pi Hardware Watchdog
  if (millis() - last_pi_heartbeat > PI_HARD_RESET_TIMEOUT_MS) {
    trigger_pi_hardware_reboot();
  }

  delay(5);
}
